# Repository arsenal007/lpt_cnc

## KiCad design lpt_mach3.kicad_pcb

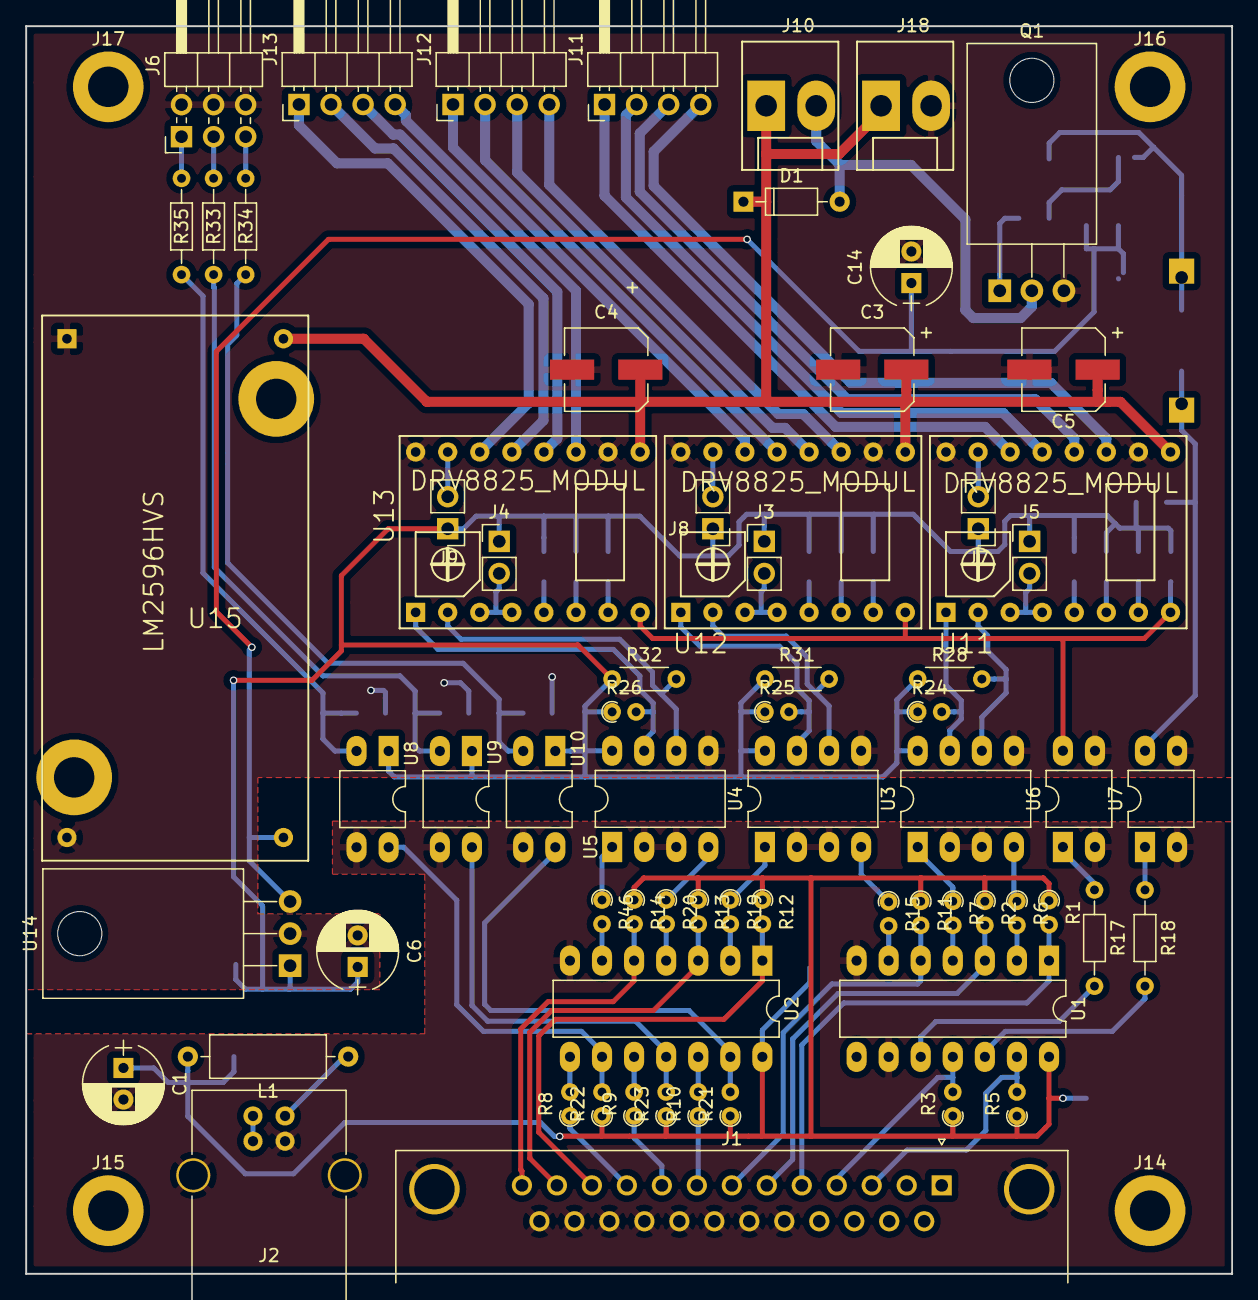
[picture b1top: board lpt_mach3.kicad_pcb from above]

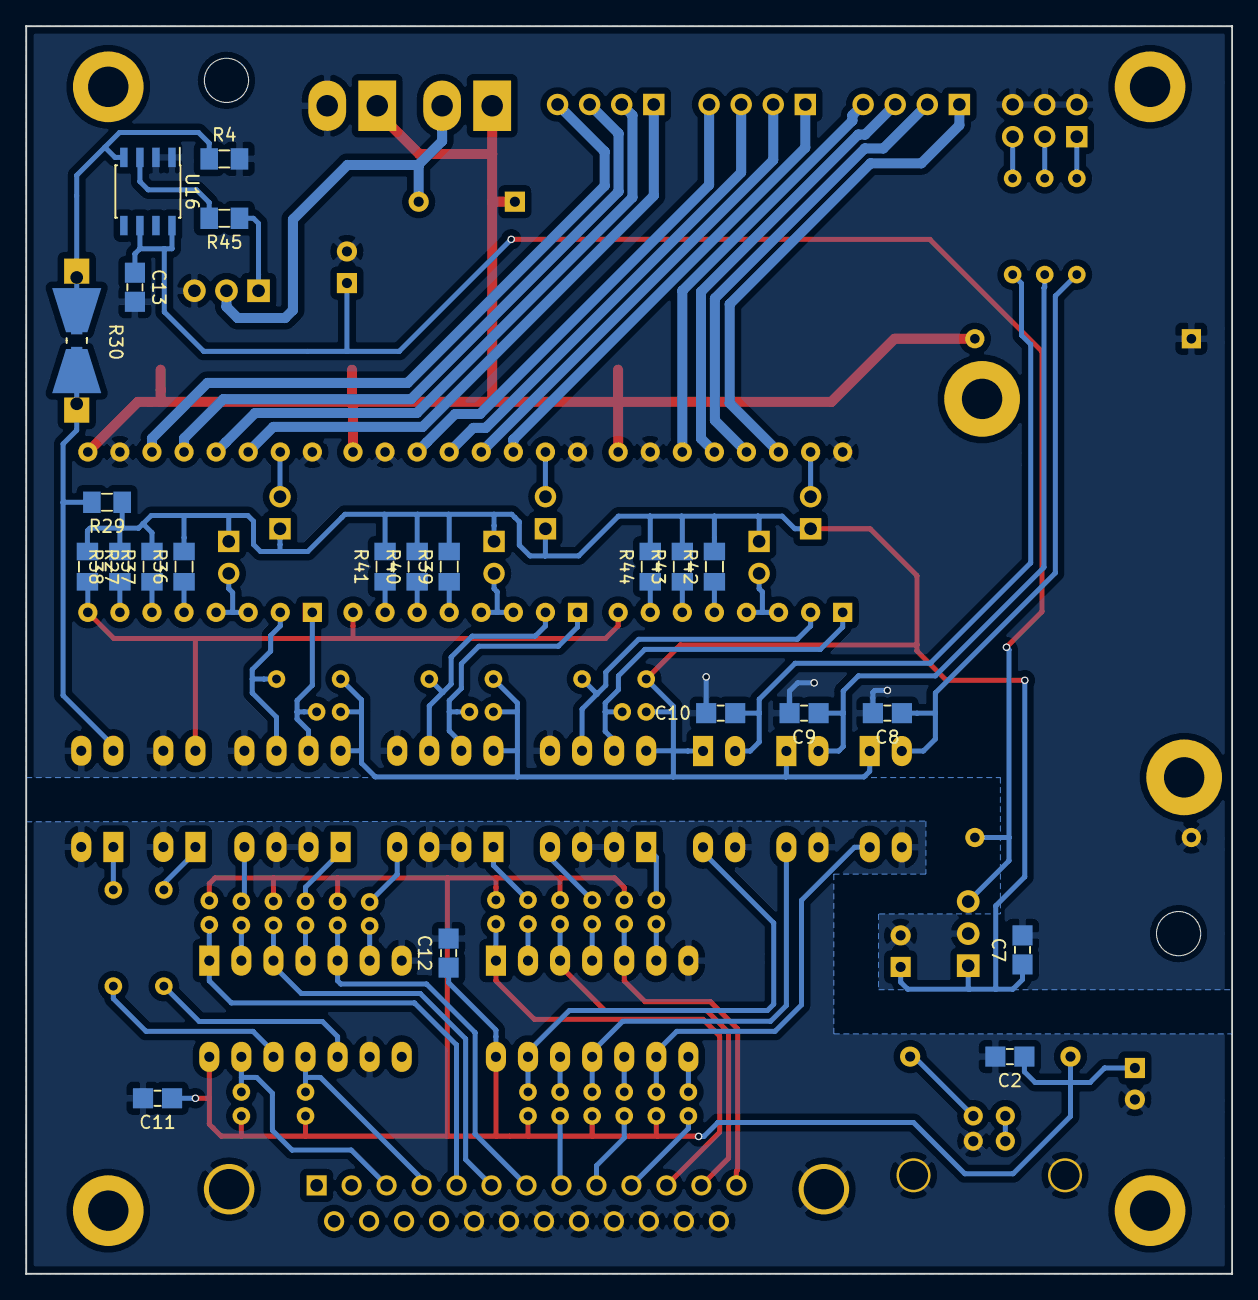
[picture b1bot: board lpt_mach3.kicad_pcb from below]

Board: 2 copper layers, 95.5 x 98.8 mm, 96 parts (23 on the bottom side), 86 nets.

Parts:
C1, C6, C14: 220uF; CP_Radial_D6.3mm_P2.50mm
C2, C7, C8, C9, C10, C11, C12, C13: 100nF; C_1206_0603
C3, C4, C5: 47uF; CP_Elec_6.3x5.7
D1: 1N4001; D_DO-35_SOD27_P7.62mm_Horizontal
J1: DB25_Female_MountingHoles; DSUB-25_Female_Horizontal_P2.77x2.84mm_EdgePinOffset4.94mm_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
J2: USB_B
J3, J4, J5, J7, J8, J9: DRV8825/A4988; Pin_Header_Straight_1x02_Pitch2.54mm
J6: LIMITS; Pin_Header_Angled_2x03_Pitch2.54mm
J10: SPINDLE; Molex_KK-41791-02_02x3.96mm_Straight
J11, J12, J13: Conn_01x04; PinHeader_1x04_P2.54mm_Horizontal
J14, J15, J16, J17: Conn_01x01; MountingHole_3.2mm_M3_DIN965_Pad
J18: 36v; Molex_KK-41791-02_02x3.96mm_Straight
L1: 33uH; R_Axial_DIN0309_L9.0mm_D3.2mm_P12.70mm_Horizontal
Q1: IRF540N; TO-220-3_Horizontal
R1, R2, R3, R5, R11, R12, R13, R14, R21, R22, R23: 4.7k; R_Axial_DIN0204_L3.6mm_D1.6mm_P1.90mm_Vertical
R4: 1k; R_1206_0603
R6, R7, R8, R9, R10, R15, R19, R20, R46: 470; R_Axial_DIN0204_L3.6mm_D1.6mm_P1.90mm_Vertical
R17, R18, R33, R34, R35: 470; R_Axial_DIN0204_L3.6mm_D1.6mm_P7.62mm_Horizontal
R24, R25, R26: 1.2k; R_Axial_DIN0204_L3.6mm_D1.6mm_P1.90mm_Vertical
R27, R29: 1.2k; R_1206_0603
R28, R31, R32: 1.2k; R_Axial_DIN0204_L3.6mm_D1.6mm_P5.08mm_Horizontal
R30: 6.8k; Resistor_SMD+THTuniversal_0603to2512_RM10_HandSoldering
R36, R37, R38, R39, R40, R41, R42, R43, R44: 470; R_1206_0603
R45: 4R7; R_1206_0603
U1, U2: 74HC14; DIP-14_W7.62mm_LongPads
U3, U4, U5: HCPL2630; DIP-8_W7.62mm_LongPads
U6, U7, U8, U9, U10: PC817; DIP-4_W7.62mm_LongPads
U11, U12, U13: DRV8825_MODUL; DRV8825
U14: L7805; TO-220-3_Horizontal
U15: LM2596HVS; LM2596HVS_MODUL
U16: NE555; SOIC-8_3.9x4.9mm_Pitch1.27mm

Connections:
+5VA: C6.1, C7.1, J3.1, J4.1, J5.1, J7.1, J8.1, J9.1, R24.1, R25.1, R26.1, R27.1, R28.1, R29.1, R31.1, R32.1, R36.2, R37.2, R38.2, R39.2, R40.2, R41.2, R42.2, R43.2, R44.2, U3.8, U4.8, U5.8, U8.1, U9.1, U10.1, U14.1
+5VD: C1.1, C2.1, C11.1, C12.1, L1.2, R1.1, R2.1, R3.1, R5.1, R11.1, R12.1, R13.1, R14.1, R21.1, R22.1, R23.1, U1.14, U2.14
+12V: C13.1, C14.1, U14.3, U15.3, U16.6, U16.8
+36V: C3.1, C4.1, C5.1, D1.1, J10.1, J18.1, U11.9, U12.9, U13.9, U15.2
/X-DIR: J1.6, R2.2, U1.3
/X-STEP: J1.5, R1.2, U1.1
/Y-DIR: J1.7, R11.2, U1.5
/Y-STEP: J1.11, R12.2, U2.1
/Z-DIR: J1.13, R14.2, U2.5
/Z-STEP: J1.12, R13.2, U2.3
GND: C1.2, C2.2, C11.2, C12.2, J1.0, J1.18, J1.19, J1.20, J1.21, J1.22, J1.23, J1.24, J1.25, J2.4, J2.5, U1.7, U1.9, U2.7, U3.2, U3.3, U4.2, U4.3, U5.2, U5.3, U6.2, U7.2, U8.3, U9.3, U10.3
GNDA: C3.2, C4.2, C5.2, C6.2, C7.2, C8.2, C9.2, C10.2, C13.2, C14.2, J6.2, J6.4, J6.6, J18.2, Q1.3, R4.2, U3.5, U4.5, U5.5, U6.3, U7.3, U11.10, U11.16, U12.10, U12.16, U13.10, U13.16, U14.2, U15.1, U15.4, U16.1, U16.2
unnamed: C8.1, R35.2, U8.2
unnamed: C9.1, R33.2, U9.2
unnamed: C10.1, R34.2, U10.2
unnamed: D1.2, J10.2, Q1.2
unnamed: J1.3, R5.2, U1.13
unnamed: J1.4, R3.2, U1.11
unnamed: J1.8, R10.1
unnamed: J1.9, R9.1
unnamed: J1.10, R8.1
unnamed: J2.1, L1.1
unnamed: J2.2, J2.3
unnamed: J3.2, U12.3, U12.4
unnamed: J4.2, U13.3, U13.4
unnamed: J5.2, U11.3, U11.4
unnamed: J6.1, R35.1
unnamed: J6.3, R33.1
unnamed: J6.5, R34.1
unnamed: J7.2, U11.15
unnamed: J8.2, U12.15
unnamed: J9.2, U13.15
unnamed: J11.1, U11.14
unnamed: J11.2, U11.13
unnamed: J11.3, U11.12
unnamed: J11.4, U11.11
unnamed: J12.1, U12.14
unnamed: J12.2, U12.13
unnamed: J12.3, U12.12
unnamed: J12.4, U12.11
unnamed: J13.1, U13.14
unnamed: J13.2, U13.13
unnamed: J13.3, U13.12
unnamed: J13.4, U13.11
unnamed: Q1.1, R45.1
unnamed: R6.1, U3.4
unnamed: R6.2, U1.2
unnamed: R7.1, U3.1
unnamed: R7.2, U1.4
unnamed: R8.2, U2.8
unnamed: R9.2, U2.10
unnamed: R10.2, U2.12
unnamed: R15.1, U4.4
unnamed: R15.2, U1.6
unnamed: R17.1, U6.1
unnamed: R17.2, U1.10
unnamed: R18.1, U7.1
unnamed: R18.2, U1.12
unnamed: R19.1, U4.1
unnamed: R19.2, U2.2
unnamed: R20.1, U5.4
unnamed: R20.2, U2.4
unnamed: R21.2, U2.13, U10.4
unnamed: R22.2, U2.9, U8.4
unnamed: R23.2, U2.11, U9.4
unnamed: R24.2, U3.7, U11.1
unnamed: R25.2, U4.7, U12.1
unnamed: R26.2, U5.7, U13.1
unnamed: R27.2, U6.4, U11.8, U12.8, U13.8
unnamed: R28.2, U3.6, U11.2
unnamed: R29.2, R30.2, U7.4
unnamed: R4.1, R30.1, U16.4
unnamed: R31.2, U4.6, U12.2
unnamed: R32.2, U5.6, U13.2
unnamed: R36.1, U11.5
unnamed: R37.1, U11.6
unnamed: R38.1, U11.7
unnamed: R39.1, U12.5
unnamed: R40.1, U12.6
unnamed: R41.1, U12.7
unnamed: R42.1, U13.5
unnamed: R43.1, U13.6
unnamed: R44.1, U13.7
unnamed: R45.2, U16.3
unnamed: R46.1, U5.1
unnamed: R46.2, U2.6
